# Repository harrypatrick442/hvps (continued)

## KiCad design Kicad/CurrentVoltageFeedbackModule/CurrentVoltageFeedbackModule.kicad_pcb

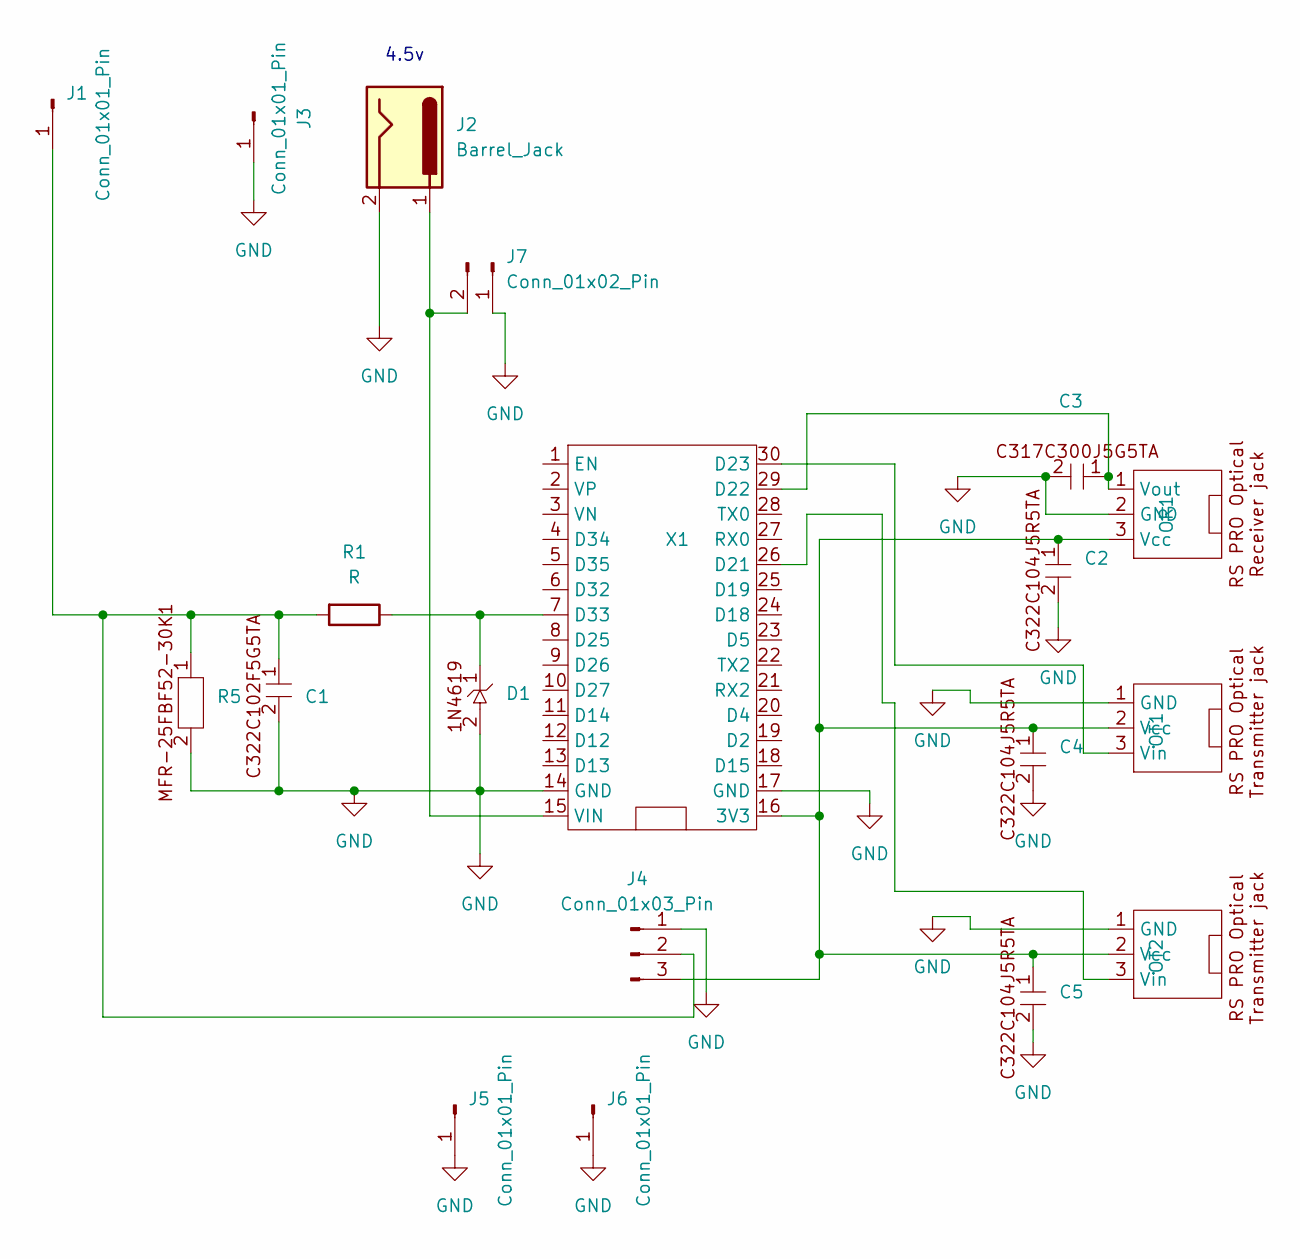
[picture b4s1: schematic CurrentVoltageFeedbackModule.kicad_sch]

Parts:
C1, C2, C3, C4, C5: C_Rect_L7.0mm_W2.5mm_P5.00mm
D1: D_DO-35_SOD27_P7.62mm_Horizontal
J1, J3: Conn_01x01_Pin; VersatilePad
J2: Barrel_Jack; BarrelJack_Horizontal
J4: Conn_01x03_Pin; PinHeader_1x03_P2.54mm_Vertical
J5, J6: Conn_01x01_Pin; ContactViaM2_5
J7: Conn_01x02_Pin; PinHeader_1x02_P2.54mm_Vertical
OR1: RS PRO Optical Receiver jack
OT1, OT2: RS Pro Optical Transmitter jack
R1: R; R_Axial_DIN0207_L6.3mm_D2.5mm_P5.08mm_Vertical
R5: R_Axial_DIN0207_L6.3mm_D2.5mm_P10.16mm_Horizontal
X1: ESP32_WROOM-32_Dev_Board

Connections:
GND: C1.2, C2.2, C3.2, C4.2, C5.2, D1.2, J2.2, J3.1, J4.1, J5.1, J6.1, J7.1, OR1.2 (GND), OT1.1 (GND), OT2.1 (GND), R5.2, X1.14 (GND), X1.17 (GND)
unnamed: C1.1, J1.1, J4.2, R1.2, R5.1
unnamed: C2.1, C4.1, C5.1, J4.3, OR1.3 (Vcc), OT1.2 (Vcc), OT2.2 (Vcc), X1.16 (3V3)
unnamed: J2.1, J7.2, X1.15 (VIN)
unnamed: C3.1, OR1.1 (Vout), X1.29 (D22)
unnamed: OT1.3 (Vin), X1.30 (D23)
unnamed: OT2.3 (Vin), X1.26 (D21)
unnamed: D1.1, R1.1, X1.7 (D33)

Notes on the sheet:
4.5v

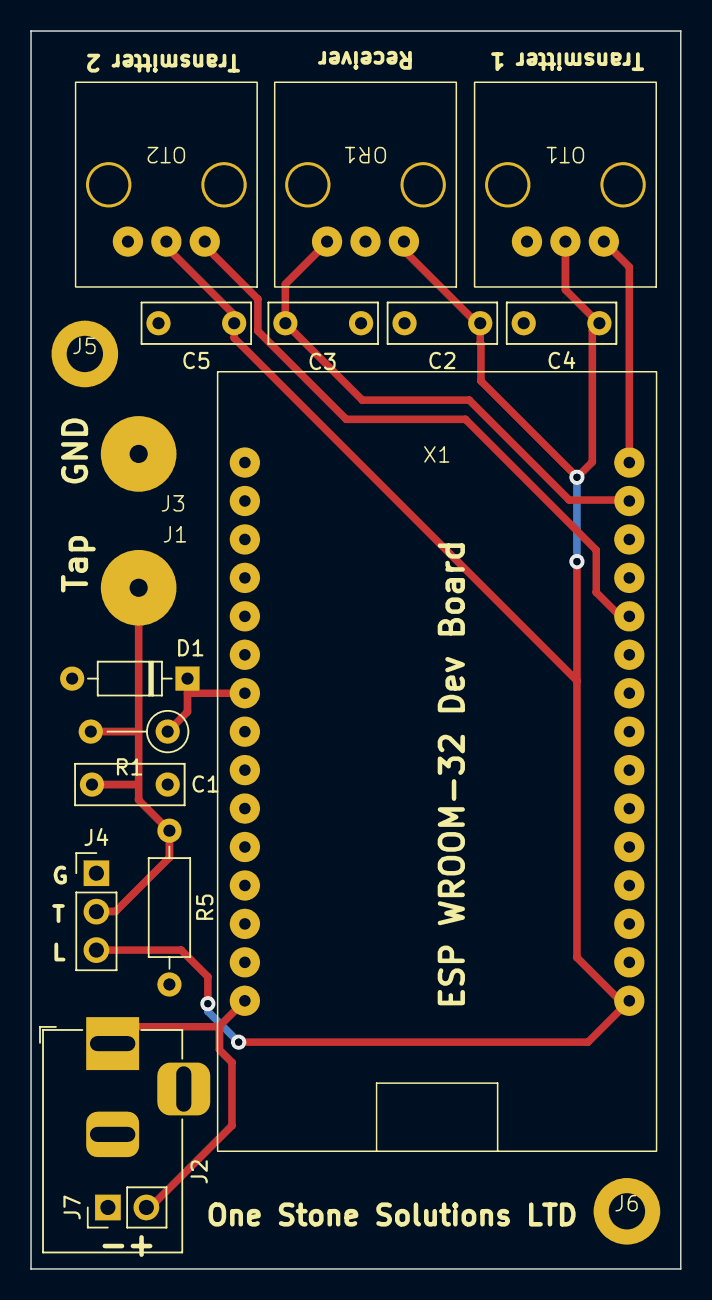
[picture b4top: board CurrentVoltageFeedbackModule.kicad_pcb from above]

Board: 2 copper layers, 42.9 x 81.8 mm, 19 parts (0 on the bottom side), 8 nets.

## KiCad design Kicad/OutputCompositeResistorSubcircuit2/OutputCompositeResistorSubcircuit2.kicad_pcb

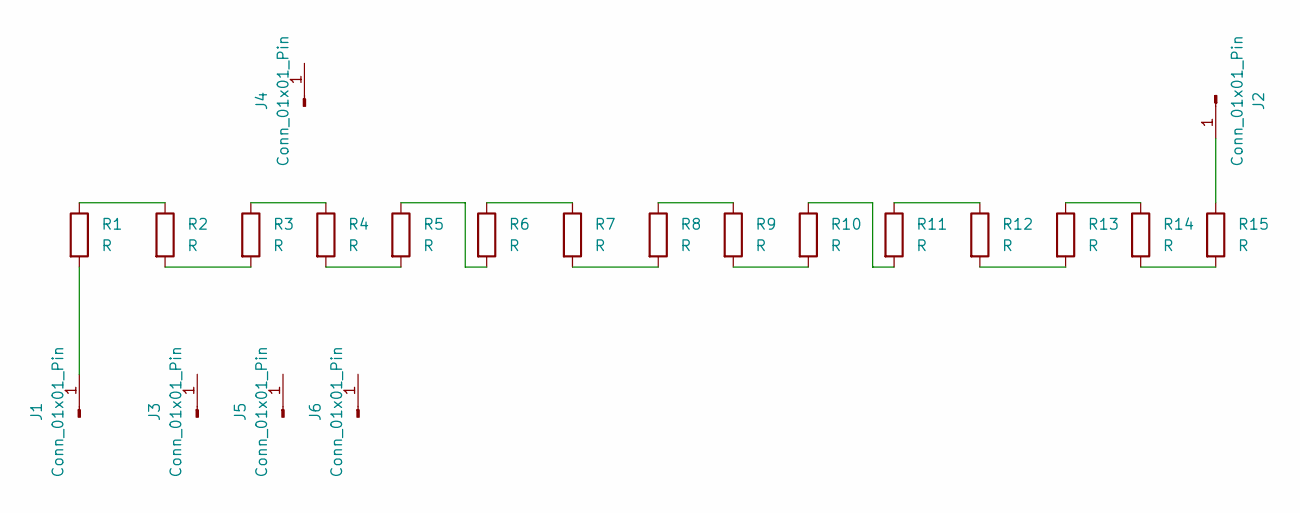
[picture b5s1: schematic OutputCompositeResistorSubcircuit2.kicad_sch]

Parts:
J1, J2: Conn_01x01_Pin; VersatilePad
J3, J4, J5, J6: Conn_01x01_Pin; M3Hole
R1, R2, R3, R4, R5, R6, R7, R8, R9, R10, R11, R12, R13, R14, R15: R; HVR82MY5010

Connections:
unnamed: J1.1, R1.2
unnamed: J2.1, R15.1
unnamed: R1.1, R2.1
unnamed: R2.2, R3.2
unnamed: R3.1, R4.1
unnamed: R4.2, R5.2
unnamed: R5.1, R6.2
unnamed: R6.1, R7.1
unnamed: R7.2, R8.2
unnamed: R8.1, R9.1
unnamed: R10.1, R11.2
unnamed: R9.2, R10.2
unnamed: R11.1, R12.1
unnamed: R12.2, R13.2
unnamed: R13.1, R14.1
unnamed: R14.2, R15.2

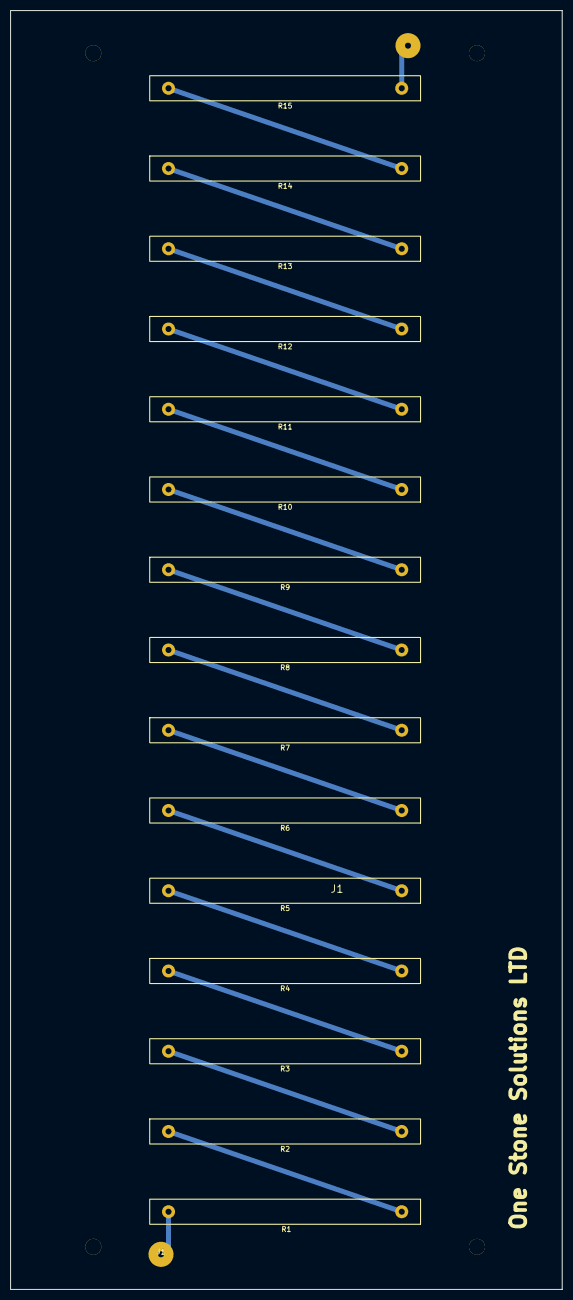
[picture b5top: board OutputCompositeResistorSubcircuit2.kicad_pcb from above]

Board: 2 copper layers, 110.0 x 255.0 mm, 21 parts (0 on the bottom side), 16 nets.

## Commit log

2025-09-17 Initial commit
    High voltage power supply I have been engineering for some experiments related to a high energy plasma anomaly I observed as a teenager which I speculate was basically small scale ball-lightning. Thi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
2025-09-18 Reorganising is going nicely.
2025-09-25 Now building again nicely.
2025-09-29 going good.
2025-10-01 Finally building :D. Now back to the voltage feedback module for the tweaks required.
2025-10-05 Getting there
    Major refactoring splitting into dependency components. Shared and VoltageFeedbackModuleBase :) OutputVoltageFeedbackModule, FirstStageFeedbackModule, HVPSController are top level projects.
2025-10-13 All now building. Had to tweak the design slightly to use
    Had to tweak the design to use twelve https://www.aliexpress.com/item/1005005011684166.html in series as the output current limiting resistor. This gives me superior value for money and limits the ou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
2025-10-16 DebugAndOtherPeripheralsBoard
2025-10-25 ProgrammingHelper
    Utility that has buttons to quickly spin up the console if not open and send commands for configuring building flashing monitoring. This automatically establishes the com port to avoid confusion by m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
2025-10-28 Sorting out simple little quick ui to run esp32 idf commands
    and sorted out flash methods for strings. These are going to required for buffering the last error message if an abort happens so it can be retrieved on reboot and passed to the UI.
2025-10-30 Implementing caching of error information for panic and abort and the like
    This will allow real time error feedback to the ui when the device is running incase of a panic or anything.
2025-11-02 panic logging seems to be working nicely and putting in place events on
    putting in place onOpen and onClosed events on IChannelEvents which is inherited by IChannel and a base class ChannelEvents makes easily available. These events must be dispatched in order from the p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
2025-11-06 Going great. Lets just get it committed.
2025-11-06 CrashReporter done :)
2025-11-08 Going great
2025-11-13 Almost done with parsing panics to clients upon reboot and reconnect and the same for last abort treason and backtrace.
    I just got custom code to get the backtrace anywhere working for the Aborter::safeAbort method.
2025-11-13 Now just to finish implementing the client side printing of the backtrace array from the LastAbortMessage.
2025-11-16 Two different approaches. shared_ptr and internal memory cleanup vs CleanupBucket
    are battling it out they just met logaheads at one point in my code and i think im going with CleanupBucket for a number of reasons for this. Primarily because the message wrapper objects are not rea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
2025-11-20 Going extremely well.
    Been implementing error handling for abort and panic and stuff and thats all good now. And been modifying the HighSpeedCore to handle this appropriately. Thats all good from waht i can see. About to 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
2025-11-24 Going wonderfully well
    Implemented programmable led related stuff and created Peripheral1 which is a peripheral subsystem talked to by the main controller board over fiber optics. At present this board only controls leds i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
2025-11-26 UART now supports software UART so i can go beyond two.
2025-11-30 Going great
    I have sorted the issues with the bluetooth stack incoming event being delayed due to time consuming methods by implementing TransientWorker. And further shifted the running of system checks to a new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
2025-12-03 Going great!
    Software uart debugged, had some issues but for this particular case a low baud rate is more than fine. Coms from the main controller to the peripheral are not the problem. And those seem to work mor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
2025-12-03 Introducing MessageIntegrity
2025-12-04 RMT in place but not been debugged yet.
2025-12-04 RMT is perfect now
    Robust as fck and perfect.
2025-12-05 Think I'm finally happy with HardwareRMT. It now uses a single sync instead of start and stop
2025-12-06 Finally think im happy with HardwareRMT
2025-12-06 before i attempt to let gpt refactor it to use the new rmt api due to a conflict with an led library that
    also uses the new one. Might as well use it. I have already started it here but only with changes to includes.
2025-12-06 almost done switching to use the new api and be compatible with rmt led stuff.
2025-12-07 almost there.
2025-12-07 FINALLY. Ready to try to build. I just want to get this committed
    I am the only person working on this right now and im going to commit it as is.
2025-12-07 minor changes
    now channels are not specified directly for RMT. Now all four projects build!
2025-12-08 Building HP
2025-12-10 Going great.
2025-12-10 Perfect now :)
2025-12-10 ok now i am happy with it and ready to build
2025-12-11 Cleaned up made some changes and now builds.
2025-12-12 MRTChannel works!
2025-12-13 MRTChannel in place
    All building good. MRTChannel in place for ToslinkDuplexChannel. Next we have to implement watchdog
2025-12-15 MRT works perfectly and crc32 system now in place.
2025-12-18 Sorting out configurations and working on Emulator
2025-12-19 Switched most stuff to float as double precision not required.
2025-12-20 sorted new issue with UART and now been thinking about
    ways to shrink file size because we are running low on space for the program on HVPSController. I have a way and it massively reduces space taken by strings.
2025-12-21 in process of switching to SAFE_ABORT
2025-12-21 In process of refactoring to use SAFE_ABORT
2025-12-21 all my macro's are in place now
    So that when i want to i can write a custom precompiler stage and strip all unnecessary message string content from the compiled software.
2025-12-31 Almost done with emulation code and just sorted FrequencyMeter so its a reusable part
2026-01-02 Have the emulation working and gradually working through improvements and fixes
    and then onto the redundancy to handle any bitflips and the watchdog.
2026-01-09 Still trying to find the root cause of an issue with second run onwards
    where the main controller thinks the threshold for output voltage is in the wrong state even after setting brute force reached for the test. Want to get this on here. This could go on for sometime.
2026-01-17 Putting temperature sensing in place.
2026-01-17 started putting in place clean Watchdog system that allows different subsystems to register with different watchdog periods.
2026-01-17 low speed watchdog for slower tasks now just about sorted. Not implemented adding watchdogs just yet.
2026-01-17 Cleaned up aborter and implemented set_terminate properly.
2026-01-18 high speed core live watchdog going great. Not ran yet.
2026-01-19 need a nice structured way to automatically hand out timers and groups for hardware interrupt timers.
    I stumbled upon a but related to this and discovered this as the cause. I had used the same hw timer in both my custom MRT library and as part of a watchdog system and it caused what appeared to be a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
2026-01-21 Going great, designing an improved primary current feedback system and started work on the second version
    of the HVPSController with a huge list of improvements i have gradually put together.
2026-01-21 Volt seconds calculation for current transformer.
2026-01-22 Voltage regulators designed!
2026-01-23 Verified safe fpga pins for io all on 3.3v bus. Maths for H-Bridge going nicely :)
    I let gpt produce a list from reading the data sheet and then manually verified all pins im using are safe.
2026-01-24 Gate driver for H-Bridge design finished
2026-01-30 Not far from done with parts list for v2 of HVPSController
2026-02-02 Started on the verilog and fpga :)
2026-02-02 Pin number as frequency working all pins displaying their number as frequency
2026-02-06 having a hard time pulling myself away from this. Must stop now.
2026-02-08 PCB coming together :)
2026-02-13 Put in place emulation of the ESP32 FPGA interface in C#.
2026-02-19 Board almost done got some more checks to do first been cleaning up nicely.
2026-02-26 Going great think im ready to order the pcb!
2026-03-23 Working on the automatic generation of the fpga interface for microcontroller to speak to fpga. C++ microcontroller side almost done :)
2026-03-23 I wrote the C++ side of the generator. Went through it and diagrams and stuff with GPT then he wrote the verilog side and it looks pretty good
    may be issues with either side but very close anyway :)
2026-03-26 Soft start is now switched to PowerConditioningMonitor and it successfully opens relay on voltage drop. Need to add event it dispatches.
2026-03-29 reading from fpga to esp correctly :)
2026-04-04 FPGA interface now sorted and works perfectly
    after a slight issue with clock signals that were bouncing slightly.
2026-04-07 Sorted out speeding up fpga interface and put in place getBitArray and getByteArray
2026-04-09 Going great. Sorted out ThresholdController and constant .sv file generation.
2026-04-15 Going great!
2026-04-16 bahahhaa going so good i'll sort out these files i shouldnt have committed but already have
    a little later on.
